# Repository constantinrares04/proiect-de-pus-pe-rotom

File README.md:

# proiect-de-pus-pe-rotom
Dispozitiv pentru gestionare ingrediente si retete.

Foloseste TheMealDB API pentru a obtine retete pe baza ingredientului selectat.
Stocheaza ingredientele valabile intr-o lista.
GUI afisat pe un ecran touchscreen rezistiv.

PCB-ul contine un cip ESP-WROOM-E32, stabilizator de 3.3V, convertor USB-UART.

Utilizare:
	Rotom.cpp si Rotom.h trebuie puse in folder-ul de librarii Arduino, intr-un folder "Rotom"
	User_Setup.h trebuie copiat/mutat in folder-ul librariei TFT-eSPI.

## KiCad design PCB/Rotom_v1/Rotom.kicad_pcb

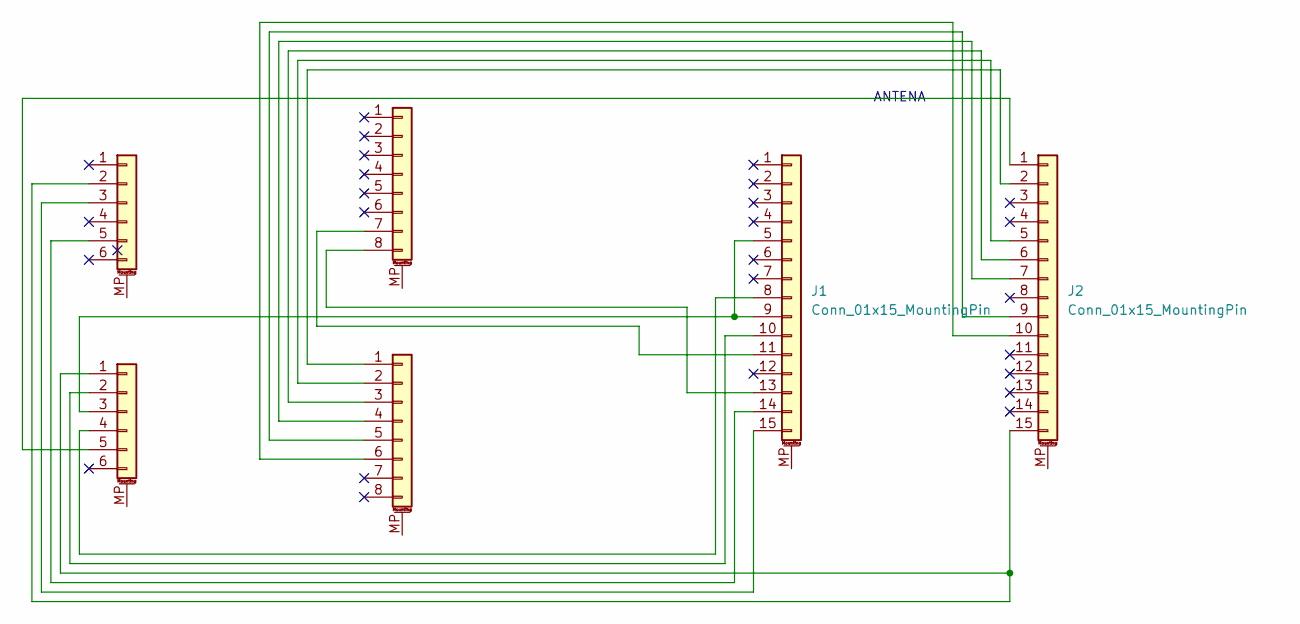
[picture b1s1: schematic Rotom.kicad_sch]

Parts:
J1, J2: Conn_01x15_MountingPin; PinSocket_1x15_P2.54mm_Vertical
J3, J4: Conn_01x08_MountingPin; PinSocket_1x08_P2.54mm_Vertical
J5, J6: Conn_01x06_MountingPin; PinSocket_1x06_P2.54mm_Vertical

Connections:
unnamed: J1.5, J1.9, J5.3
unnamed: J1.8, J5.4
unnamed: J1.10, J5.2
unnamed: J1.11, J4.7
unnamed: J1.13, J4.8
unnamed: J1.14, J6.5
unnamed: J1.15, J6.3
unnamed: J2.1, J5.5
unnamed: J2.2, J3.1
unnamed: J2.5, J3.2
unnamed: J2.6, J3.3
unnamed: J2.7, J3.4
unnamed: J2.9, J3.5
unnamed: J2.10, J3.6
unnamed: J2.15, J5.1, J6.2

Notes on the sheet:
ANTENA

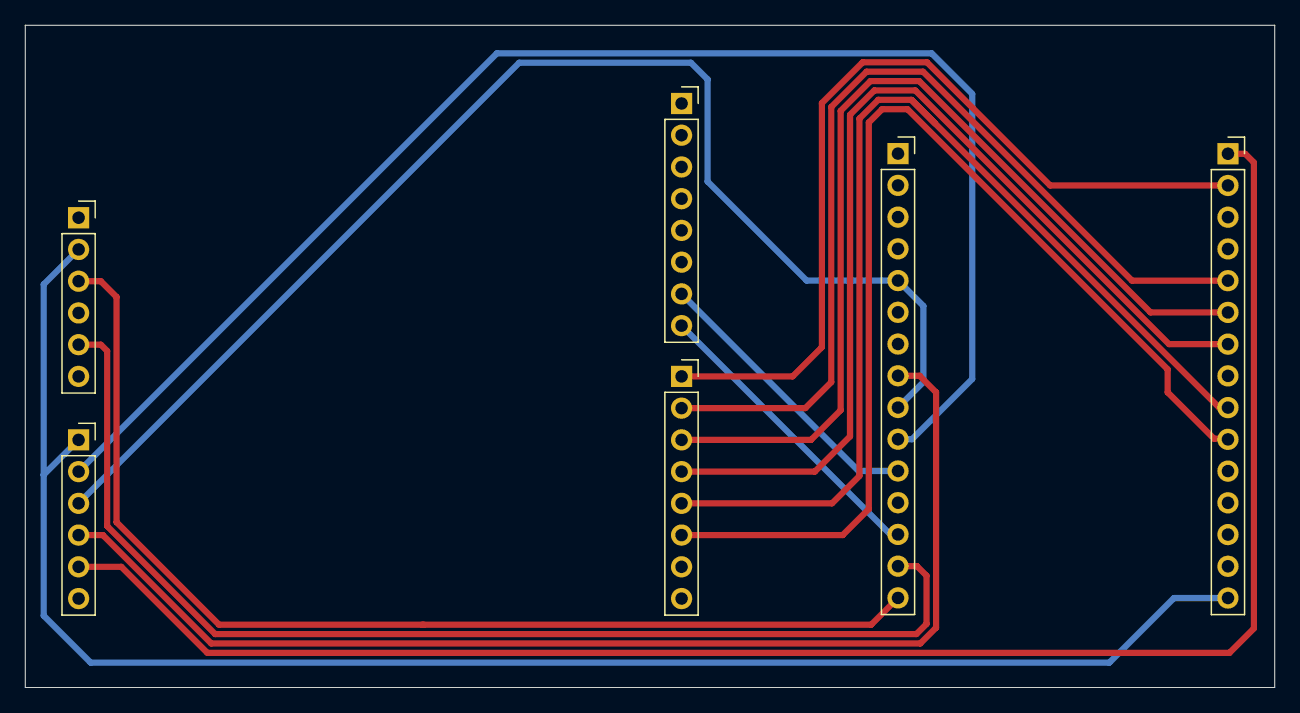
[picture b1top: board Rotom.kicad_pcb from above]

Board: 2 copper layers, 100.0 x 53.0 mm, 6 parts (0 on the bottom side), 15 nets.

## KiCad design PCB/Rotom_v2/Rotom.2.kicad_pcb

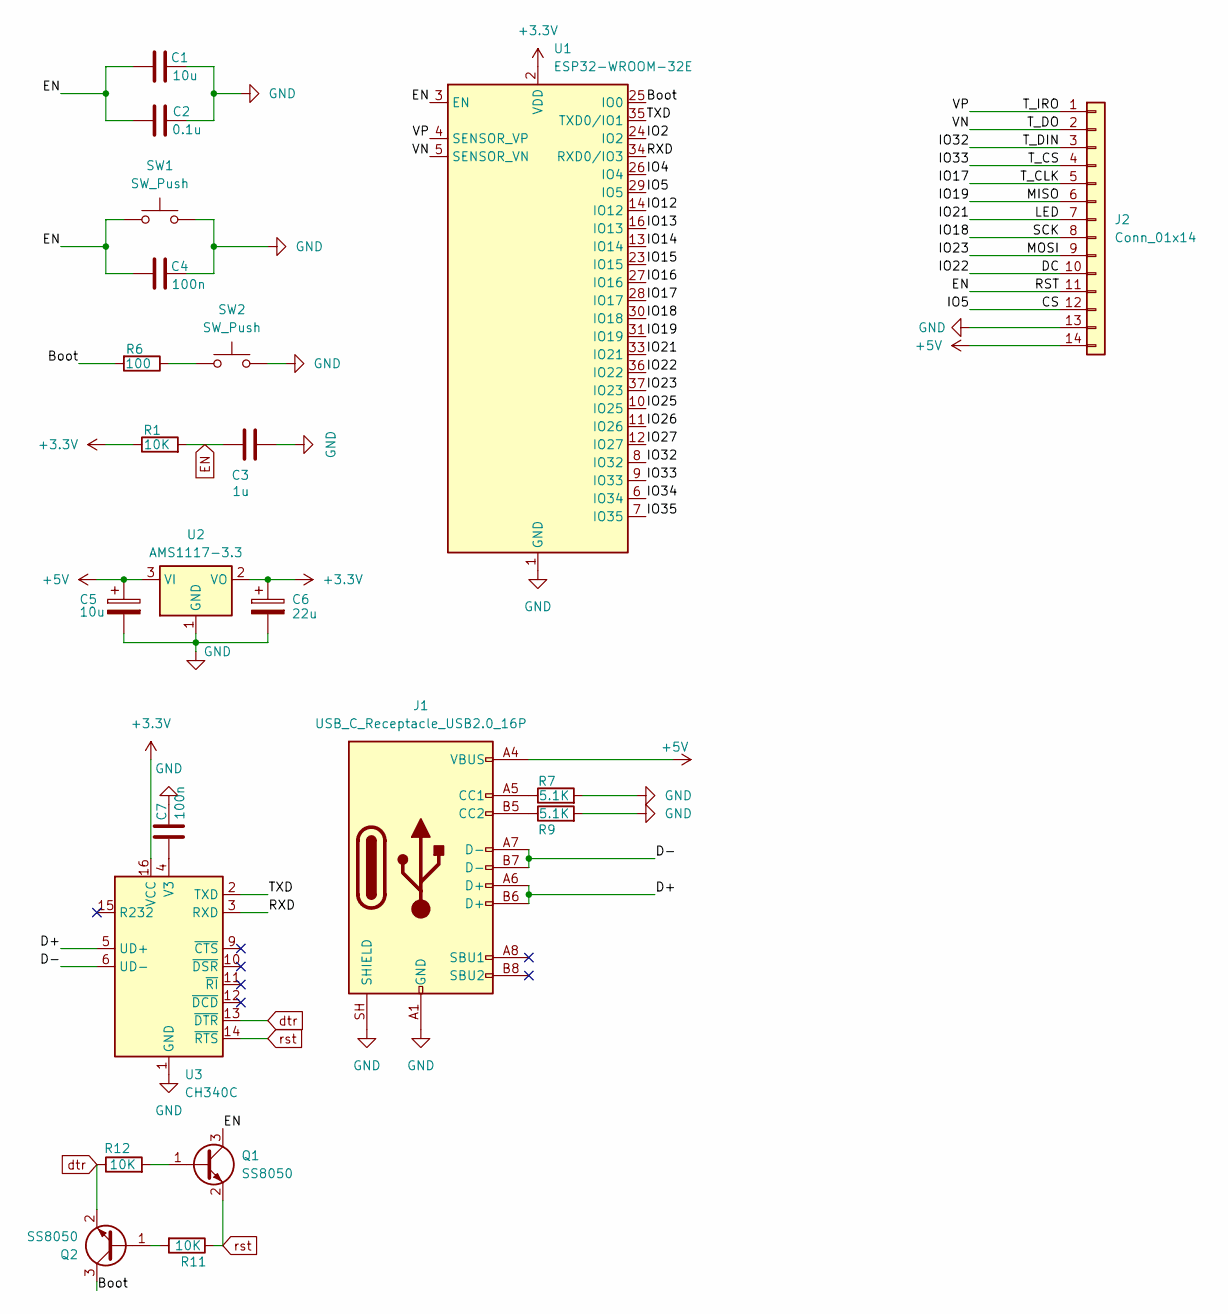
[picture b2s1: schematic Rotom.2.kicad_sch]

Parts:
C1, C5: 10u; C_0805_2012Metric_Pad1.18x1.45mm_HandSolder
C2: 0.1u; C_0805_2012Metric_Pad1.18x1.45mm_HandSolder
C3: 1u; C_0805_2012Metric_Pad1.18x1.45mm_HandSolder
C4, C7: 100n; C_0805_2012Metric_Pad1.18x1.45mm_HandSolder
C6: 22u; C_0805_2012Metric_Pad1.18x1.45mm_HandSolder
J1: USB_C_Receptacle_USB2.0_16P; USB_C_Receptacle_Amphenol_12401948E412A
J2: Conn_01x14; PinSocket_1x14_P2.54mm_Vertical
Q1, Q2: SS8050; SOT-23
R1, R11, R12: 10K; R_0805_2012Metric_Pad1.20x1.40mm_HandSolder
R6: 100; R_0805_2012Metric_Pad1.20x1.40mm_HandSolder
R7, R9: 5.1K; R_0805_2012Metric_Pad1.20x1.40mm_HandSolder
SW1, SW2: SW_Push; SW_Push_1TS009xxxx-xxxx-xxxx_6x6x5mm
U1: ESP32-WROOM-32E; ESP32-WROOM-32D
U2: AMS1117-3.3; SOT-223-3_TabPin2
U3: CH340C; SOIC-16_3.9x9.9mm_P1.27mm

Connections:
+3.3V: C6.1, R1.1, U1.2 (VDD), U2.2 (VO), U3.16 (VCC)
+5V: C5.1, J1.A4 (VBUS), J1.A9 (VBUS), J1.B4 (VBUS), J1.B9 (VBUS), J2.14, U2.3 (VI)
/Boot: Q2.3 (C), R6.2, U1.25 (IO0)
/CS: J2.12, U1.29 (IO5)
/D+: J1.A6 (D+), J1.B6 (D+), U3.5 (UD+)
/D-: J1.A7 (D-), J1.B7 (D-), U3.6 (UD-)
/DC: J2.10, U1.36 (IO22)
/IO2: U1.24 (IO2)
/IO4: U1.26 (IO4)
/IO12: U1.14 (IO12)
/IO13: U1.16 (IO13)
/IO14: U1.13 (IO14)
/IO15: U1.23 (IO15)
/IO16: U1.27 (IO16)
/IO17: J2.5, U1.28 (IO17)
/IO18: J2.8, U1.30 (IO18)
/IO19: J2.6, U1.31 (IO19)
/IO21: J2.7, U1.33 (IO21)
/IO23: J2.9, U1.37 (IO23)
/IO25: U1.10 (IO25)
/IO26: U1.11 (IO26)
/IO27: U1.12 (IO27)
/IO32: J2.3, U1.8 (IO32)
/IO33: J2.4, U1.9 (IO33)
/IO34: U1.6 (IO34)
/IO35: U1.7 (IO35)
/RXD: U1.34 (RXD0/IO3), U3.3 (RXD)
/TXD: U1.35 (TXD0/IO1), U3.2 (TXD)
/T_DO: J2.2, U1.5 (SENSOR_VN)
/T_IRO: J2.1, U1.4 (SENSOR_VP)
EN: C1.1, C2.1, C3.2, C4.1, J2.11, Q1.3 (C), R1.2, SW1.1, U1.3 (EN)
GND: C1.2, C2.2, C3.1, C4.2, C5.2, C6.2, C7.2, J1.A1 (GND), J1.A12 (GND), J1.B1 (GND), J1.B12 (GND), J1.SH (SHIELD), J2.13, R7.2, R9.2, SW1.2, SW2.2, U1.1 (GND), U1.15 (GND), U1.38 (GND), U1.39 (GND), U2.1 (GND), U3.1 (GND)
unnamed: J1.A5 (CC1), R7.1
unnamed: J1.B5 (CC2), R9.1
unnamed: Q1.1 (B), R12.2
unnamed: Q2.1 (B), R11.2
unnamed: R6.1, SW2.1
unnamed: C7.1, U3.4 (V3)
dtr: Q2.2 (E), R12.1, U3.13 (~DTR)
rst: Q1.2 (E), R11.1, U3.14 (~RTS)

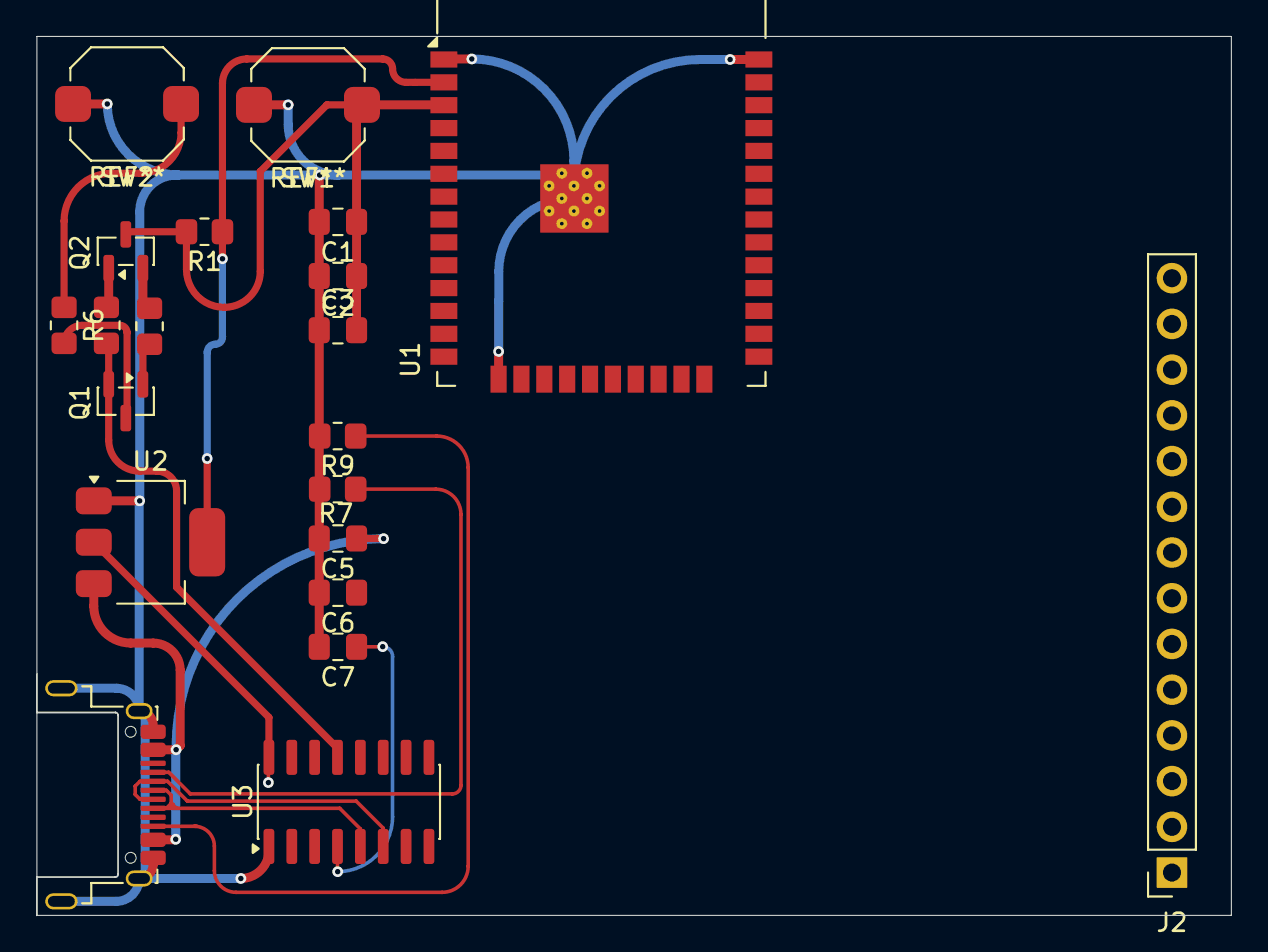
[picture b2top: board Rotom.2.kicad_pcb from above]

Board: 2 copper layers, 66.3 x 48.8 mm, 21 parts (0 on the bottom side), 28 nets.

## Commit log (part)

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2026-04-26 Add files via upload
    plm
